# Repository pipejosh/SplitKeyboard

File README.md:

# Split keyboarddd

## WHY THO??

Weeeeell my wrists kinda hurt all of a sudde, so this is such a good opportunity to learn about keyboard developemt including creating a pcb, 3d modeling and budgeting a keyboard.

This project has been so much fun, although it was a pin at the beginnig, once I  got the hang off it, oufff boy, I was so much better

This keyboard is heavily inspired by a corne keyboard, specially the key layout

# IMAGESSS!!!

### render

###  case

###  schematics

###  pcb layout

###  BOM images
## Disclaimer (The currency for this purchases is Canadian Dollars)

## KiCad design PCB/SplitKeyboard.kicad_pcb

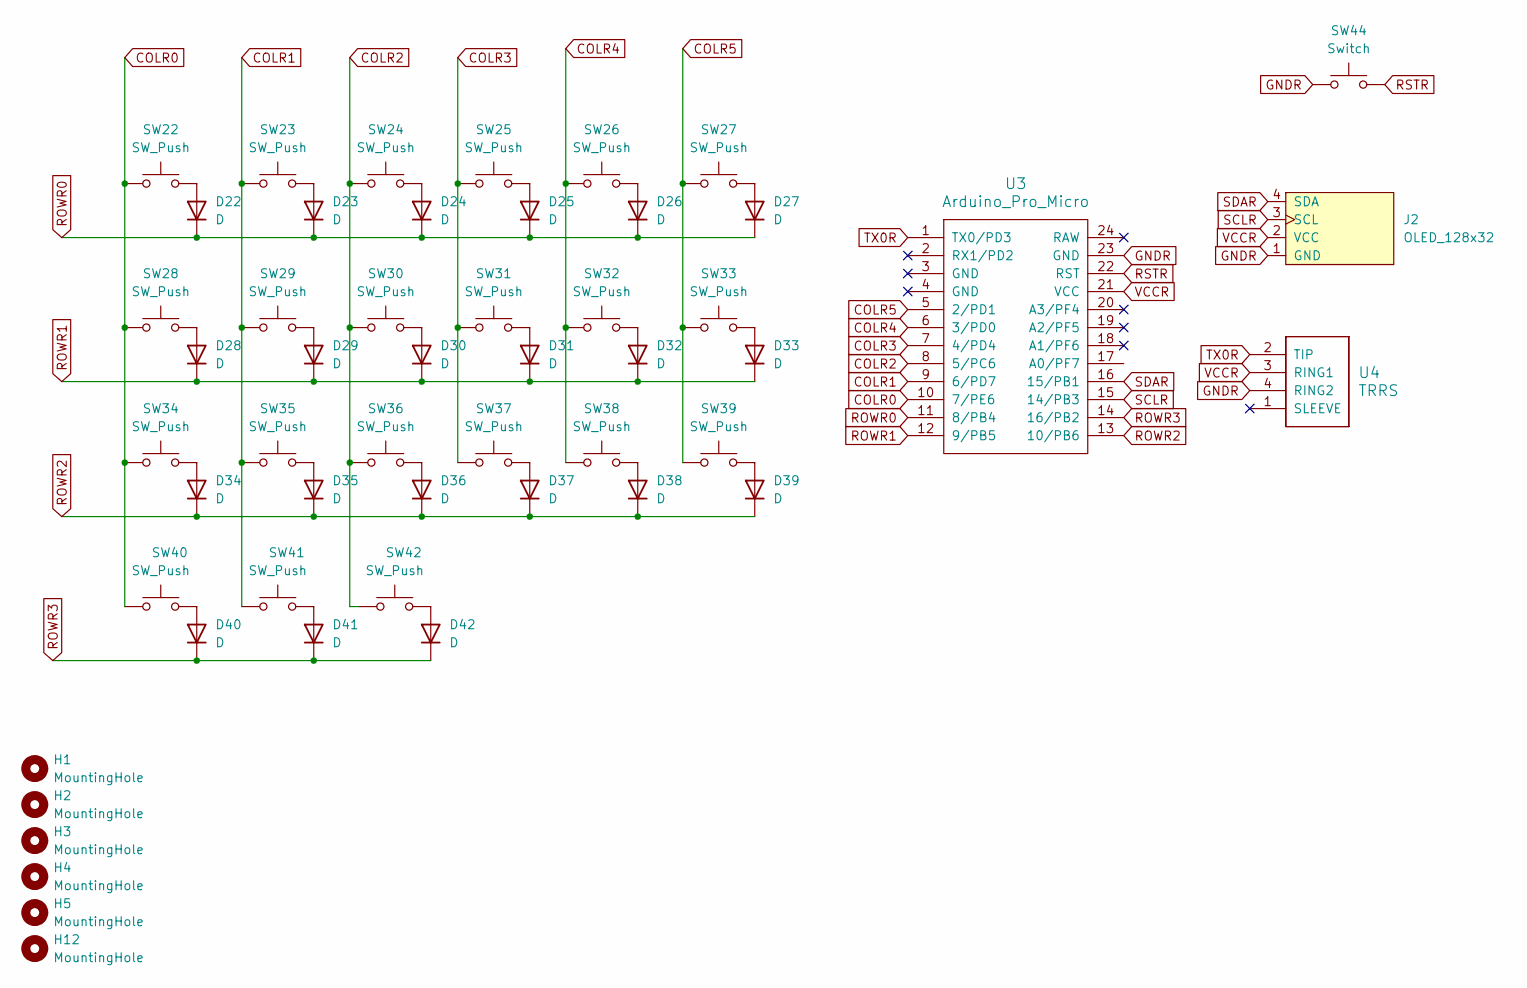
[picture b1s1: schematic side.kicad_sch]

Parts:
D22, D23, D24, D25, D26, D27, D28, D29, D30, D31, D32, D33, D34, D35, D36, D37, D38, D39, D40, D41, D42: D; Diode_SOD-123
H1, H2, H3, H4, H5, H12: MountingHole; MountingHole_2.2mm_M2
J2: OLED_128x32
SW22, SW23, SW24, SW25, SW26, SW27, SW28, SW29, SW30, SW31, SW32, SW33, SW34, SW35, SW36, SW37, SW38, SW39, SW40, SW41, SW42: SW_Push; Hotswap_MX_1.00u
SW44: Switch; Button_MJTP1243
U3: Arduino_Pro_Micro
U4: TRRS; TRRS_PJ-320A

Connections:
COLR0: SW22.1, SW28.1, SW34.1, SW40.1, U3.10 (7/PE6)
COLR1: SW23.1, SW29.1, SW35.1, SW41.1, U3.9 (6/PD7)
COLR2: SW24.1, SW30.1, SW36.1, SW42.1, U3.8 (5/PC6)
COLR3: SW25.1, SW31.1, SW37.1, U3.7 (4/PD4)
COLR4: SW26.1, SW32.1, SW38.1, U3.6 (3/PD0)
COLR5: SW27.1, SW33.1, SW39.1, U3.5 (2/PD1)
GNDR: J2.1 (GND), SW44.1, U3.23 (GND), U4.4 (RING2)
unnamed: D22.2 (A), SW22.2
unnamed: D23.2 (A), SW23.2
unnamed: D24.2 (A), SW24.2
unnamed: D25.2 (A), SW25.2
unnamed: D26.2 (A), SW26.2
unnamed: D27.2 (A), SW27.2
unnamed: D28.2 (A), SW28.2
unnamed: D29.2 (A), SW29.2
unnamed: D30.2 (A), SW30.2
unnamed: D31.2 (A), SW31.2
unnamed: D32.2 (A), SW32.2
unnamed: D33.2 (A), SW33.2
unnamed: D34.2 (A), SW34.2
unnamed: D35.2 (A), SW35.2
unnamed: D36.2 (A), SW36.2
unnamed: D37.2 (A), SW37.2
unnamed: D38.2 (A), SW38.2
unnamed: D39.2 (A), SW39.2
unnamed: D40.2 (A), SW40.2
unnamed: D41.2 (A), SW41.2
unnamed: D42.2 (A), SW42.2
ROWR0: D22.1 (K), D23.1 (K), D24.1 (K), D25.1 (K), D26.1 (K), D27.1 (K), U3.11 (8/PB4)
ROWR1: D28.1 (K), D29.1 (K), D30.1 (K), D31.1 (K), D32.1 (K), D33.1 (K), U3.12 (9/PB5)
ROWR2: D34.1 (K), D35.1 (K), D36.1 (K), D37.1 (K), D38.1 (K), D39.1 (K), U3.13 (10/PB6)
ROWR3: D40.1 (K), D41.1 (K), D42.1 (K), U3.14 (16/PB2)
RSTR: SW44.2, U3.22 (RST)
SCLR: J2.3 (SCL), U3.15 (14/PB3)
SDAR: J2.4 (SDA), U3.16 (15/PB1)
TX0R: U3.1 (TX0/PD3), U4.2 (TIP)
VCCR: J2.2 (VCC), U3.21 (VCC), U4.3 (RING1)

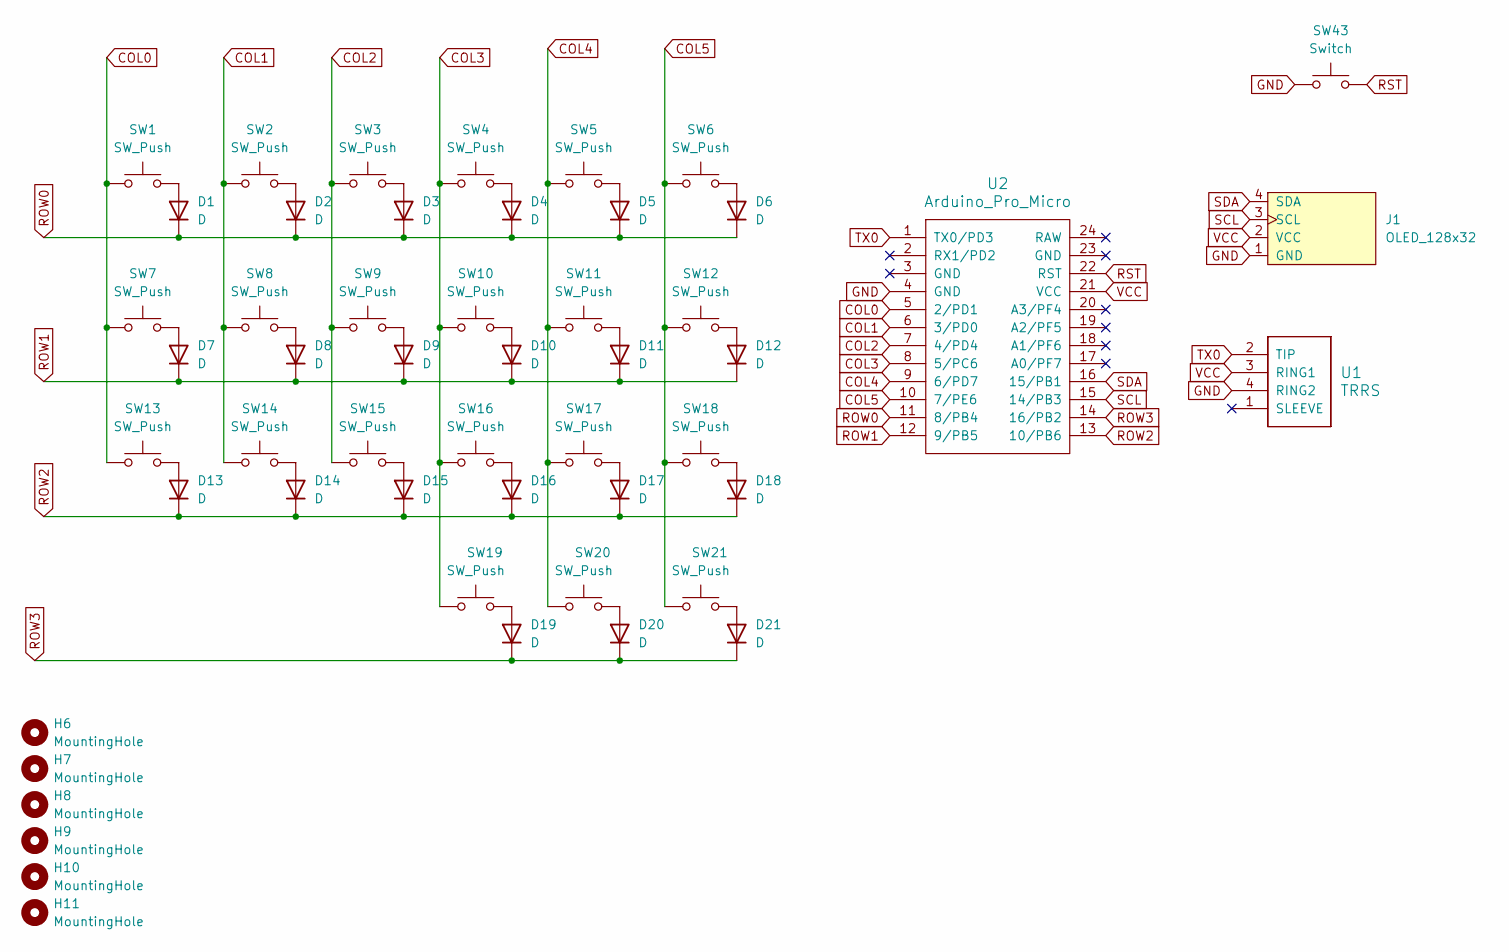
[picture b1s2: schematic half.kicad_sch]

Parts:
D1, D2, D3, D4, D5, D6, D7, D8, D9, D10, D11, D12, D13, D14, D15, D16, D17, D18, D19, D20, D21: D; Diode_SOD-123
H6, H7, H8, H9, H10, H11: MountingHole; MountingHole_2.2mm_M2
J1: OLED_128x32
SW1, SW2, SW3, SW4, SW5, SW6, SW7, SW8, SW9, SW10, SW11, SW12, SW13, SW14, SW15, SW16, SW17, SW18, SW19, SW20, SW21: SW_Push; Hotswap_MX_1.00u
SW43: Switch; Button_MJTP1243
U1: TRRS; TRRS_PJ-320A
U2: Arduino_Pro_Micro

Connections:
COL0: SW1.1, SW7.1, SW13.1, U2.5 (2/PD1)
COL1: SW2.1, SW8.1, SW14.1, U2.6 (3/PD0)
COL2: SW3.1, SW9.1, SW15.1, U2.7 (4/PD4)
COL3: SW4.1, SW10.1, SW16.1, SW19.1, U2.8 (5/PC6)
COL4: SW5.1, SW11.1, SW17.1, SW20.1, U2.9 (6/PD7)
COL5: SW6.1, SW12.1, SW18.1, SW21.1, U2.10 (7/PE6)
GND: J1.1 (GND), SW43.1, U1.4 (RING2), U2.4 (GND)
unnamed: D1.2 (A), SW1.2
unnamed: D2.2 (A), SW2.2
unnamed: D3.2 (A), SW3.2
unnamed: D4.2 (A), SW4.2
unnamed: D5.2 (A), SW5.2
unnamed: D6.2 (A), SW6.2
unnamed: D7.2 (A), SW7.2
unnamed: D8.2 (A), SW8.2
unnamed: D9.2 (A), SW9.2
unnamed: D10.2 (A), SW10.2
unnamed: D11.2 (A), SW11.2
unnamed: D12.2 (A), SW12.2
unnamed: D13.2 (A), SW13.2
unnamed: D14.2 (A), SW14.2
unnamed: D15.2 (A), SW15.2
unnamed: D16.2 (A), SW16.2
unnamed: D17.2 (A), SW17.2
unnamed: D18.2 (A), SW18.2
unnamed: D19.2 (A), SW19.2
unnamed: D20.2 (A), SW20.2
unnamed: D21.2 (A), SW21.2
ROW0: D1.1 (K), D2.1 (K), D3.1 (K), D4.1 (K), D5.1 (K), D6.1 (K), U2.11 (8/PB4)
ROW1: D7.1 (K), D8.1 (K), D9.1 (K), D10.1 (K), D11.1 (K), D12.1 (K), U2.12 (9/PB5)
ROW2: D13.1 (K), D14.1 (K), D15.1 (K), D16.1 (K), D17.1 (K), D18.1 (K), U2.13 (10/PB6)
ROW3: D19.1 (K), D20.1 (K), D21.1 (K), U2.14 (16/PB2)
RST: SW43.2, U2.22 (RST)
SCL: J1.3 (SCL), U2.15 (14/PB3)
SDA: J1.4 (SDA), U2.16 (15/PB1)
TX0: U1.2 (TIP), U2.1 (TX0/PD3)
VCC: J1.2 (VCC), U1.3 (RING1), U2.21 (VCC)

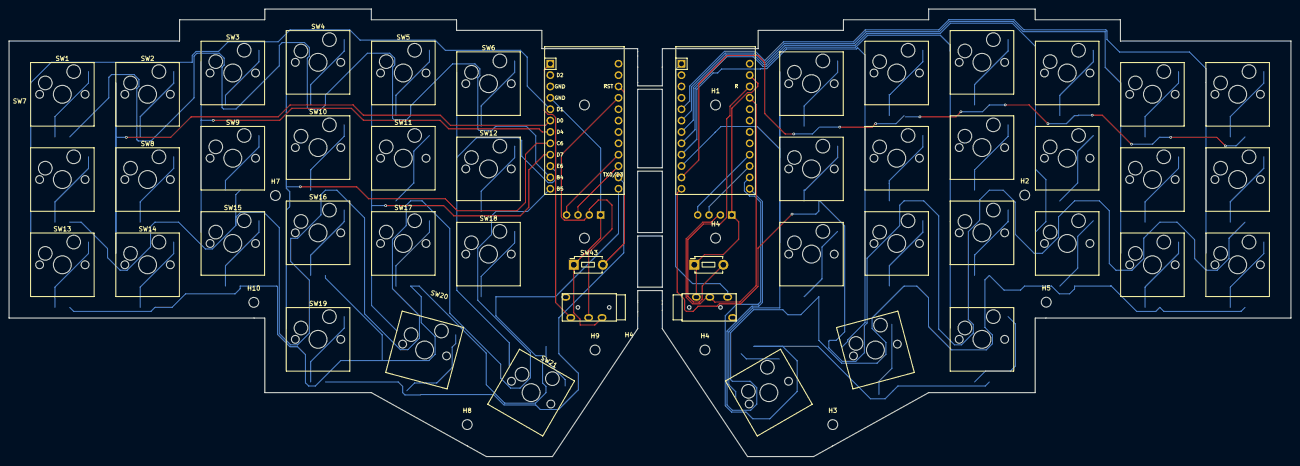
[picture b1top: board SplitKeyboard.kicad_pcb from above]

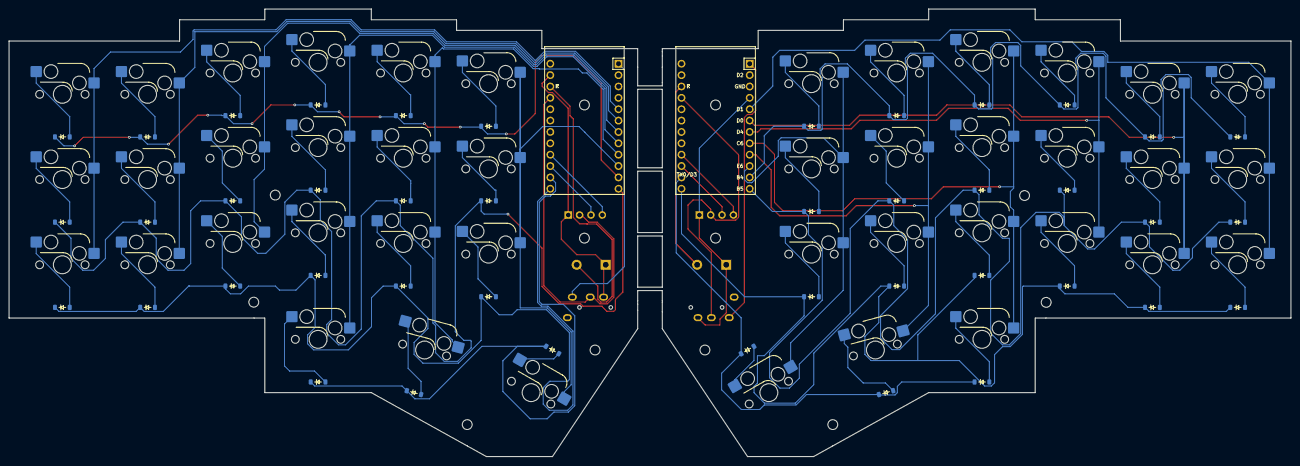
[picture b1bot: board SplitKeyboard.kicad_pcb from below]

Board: 2 copper layers, 286.5 x 100.0 mm, 104 parts (42 on the bottom side), 74 nets.

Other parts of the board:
H4#2, H4#3: MountingHole; MountingHole_2.2mm_M2

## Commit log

2025-12-07 add readme.md
2025-12-07 update render
2025-12-07 update prices
2025-12-07 edit BOM
2025-12-07 update BOM image
2025-12-16 updatae BOM
